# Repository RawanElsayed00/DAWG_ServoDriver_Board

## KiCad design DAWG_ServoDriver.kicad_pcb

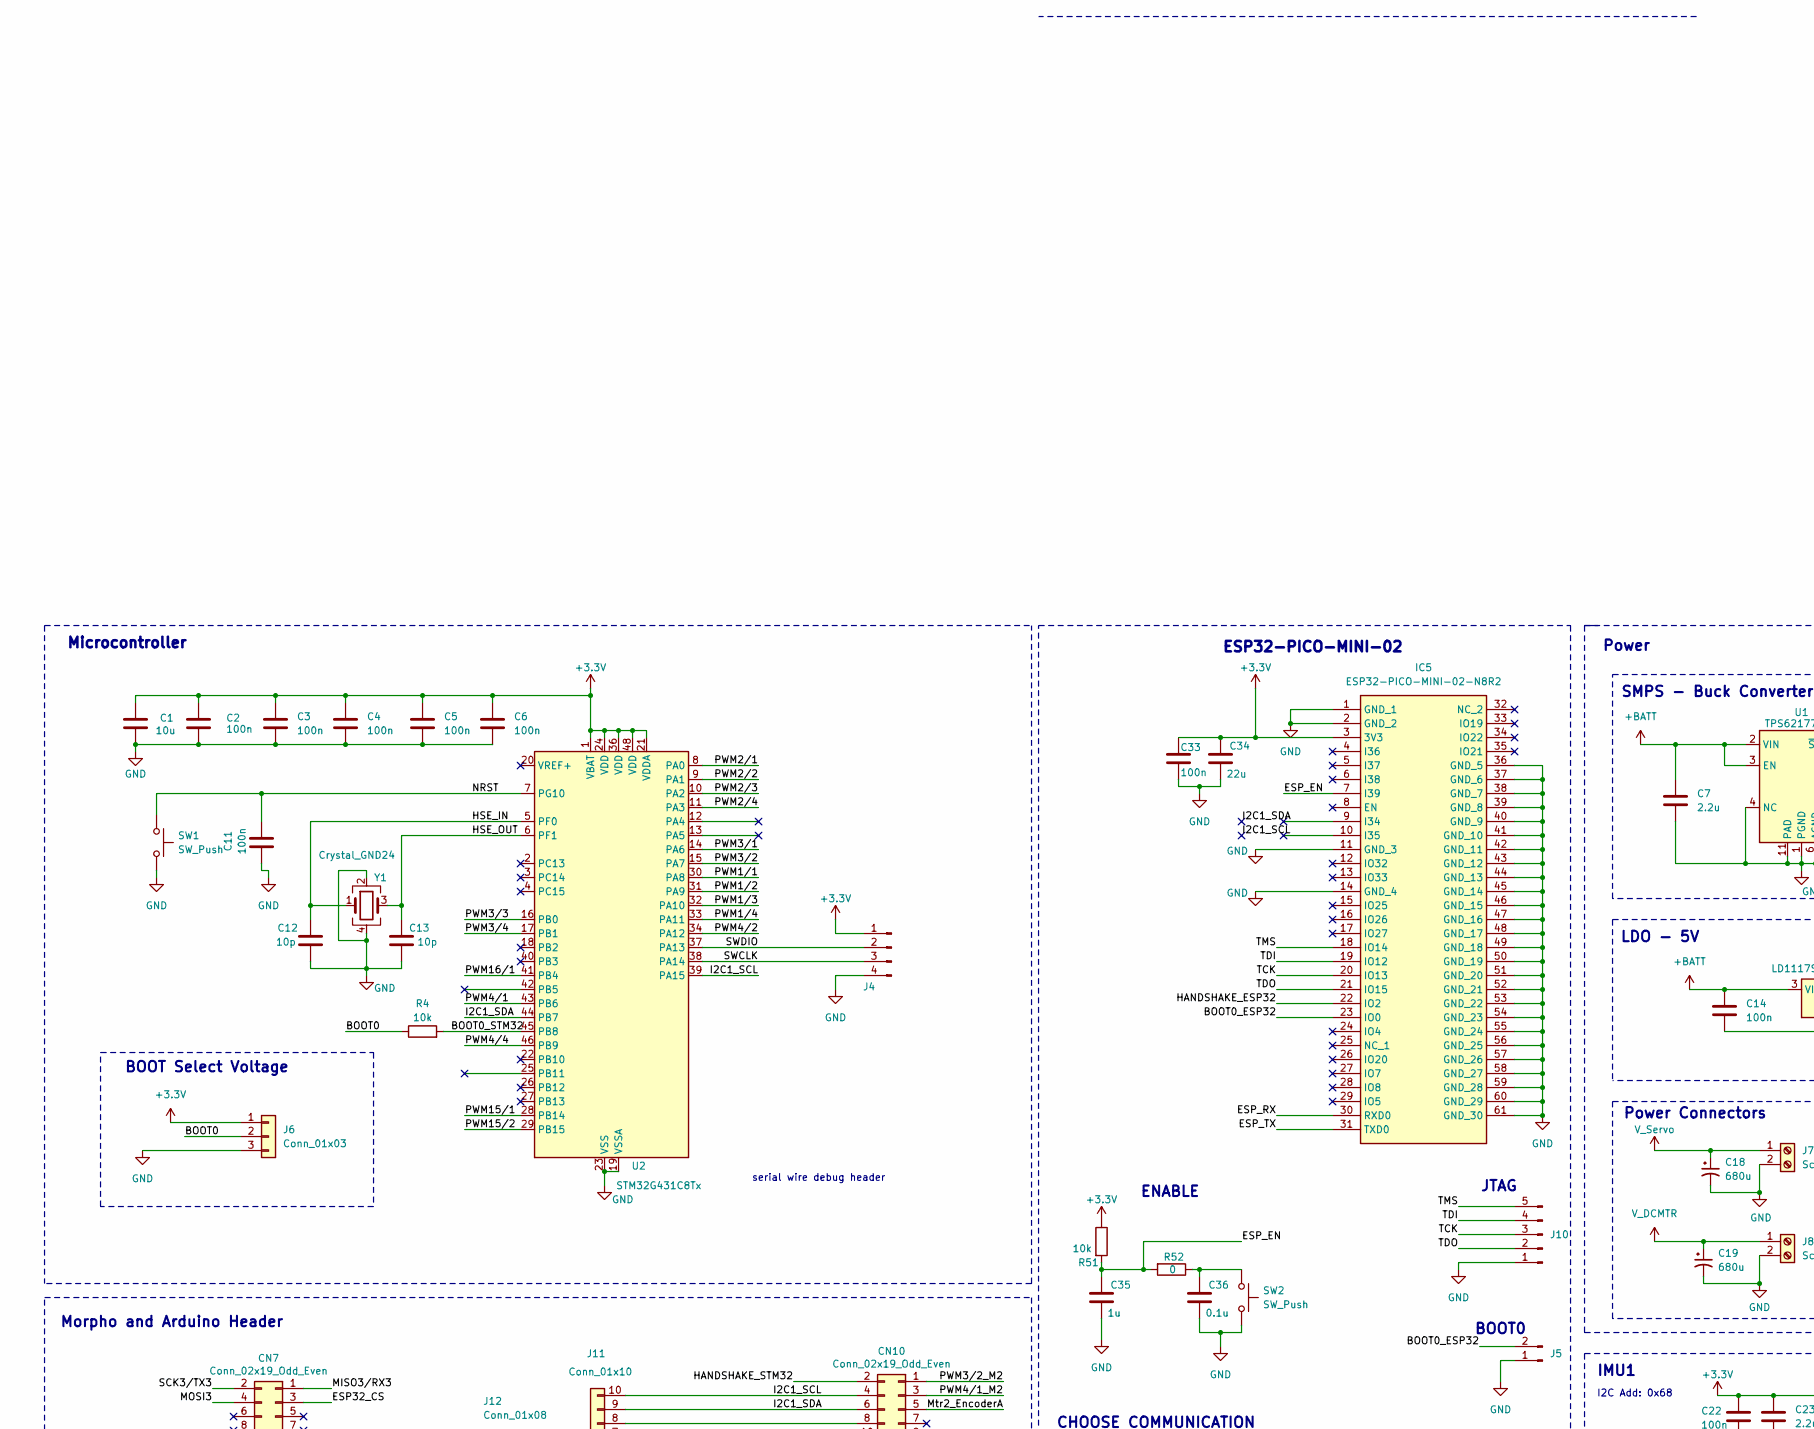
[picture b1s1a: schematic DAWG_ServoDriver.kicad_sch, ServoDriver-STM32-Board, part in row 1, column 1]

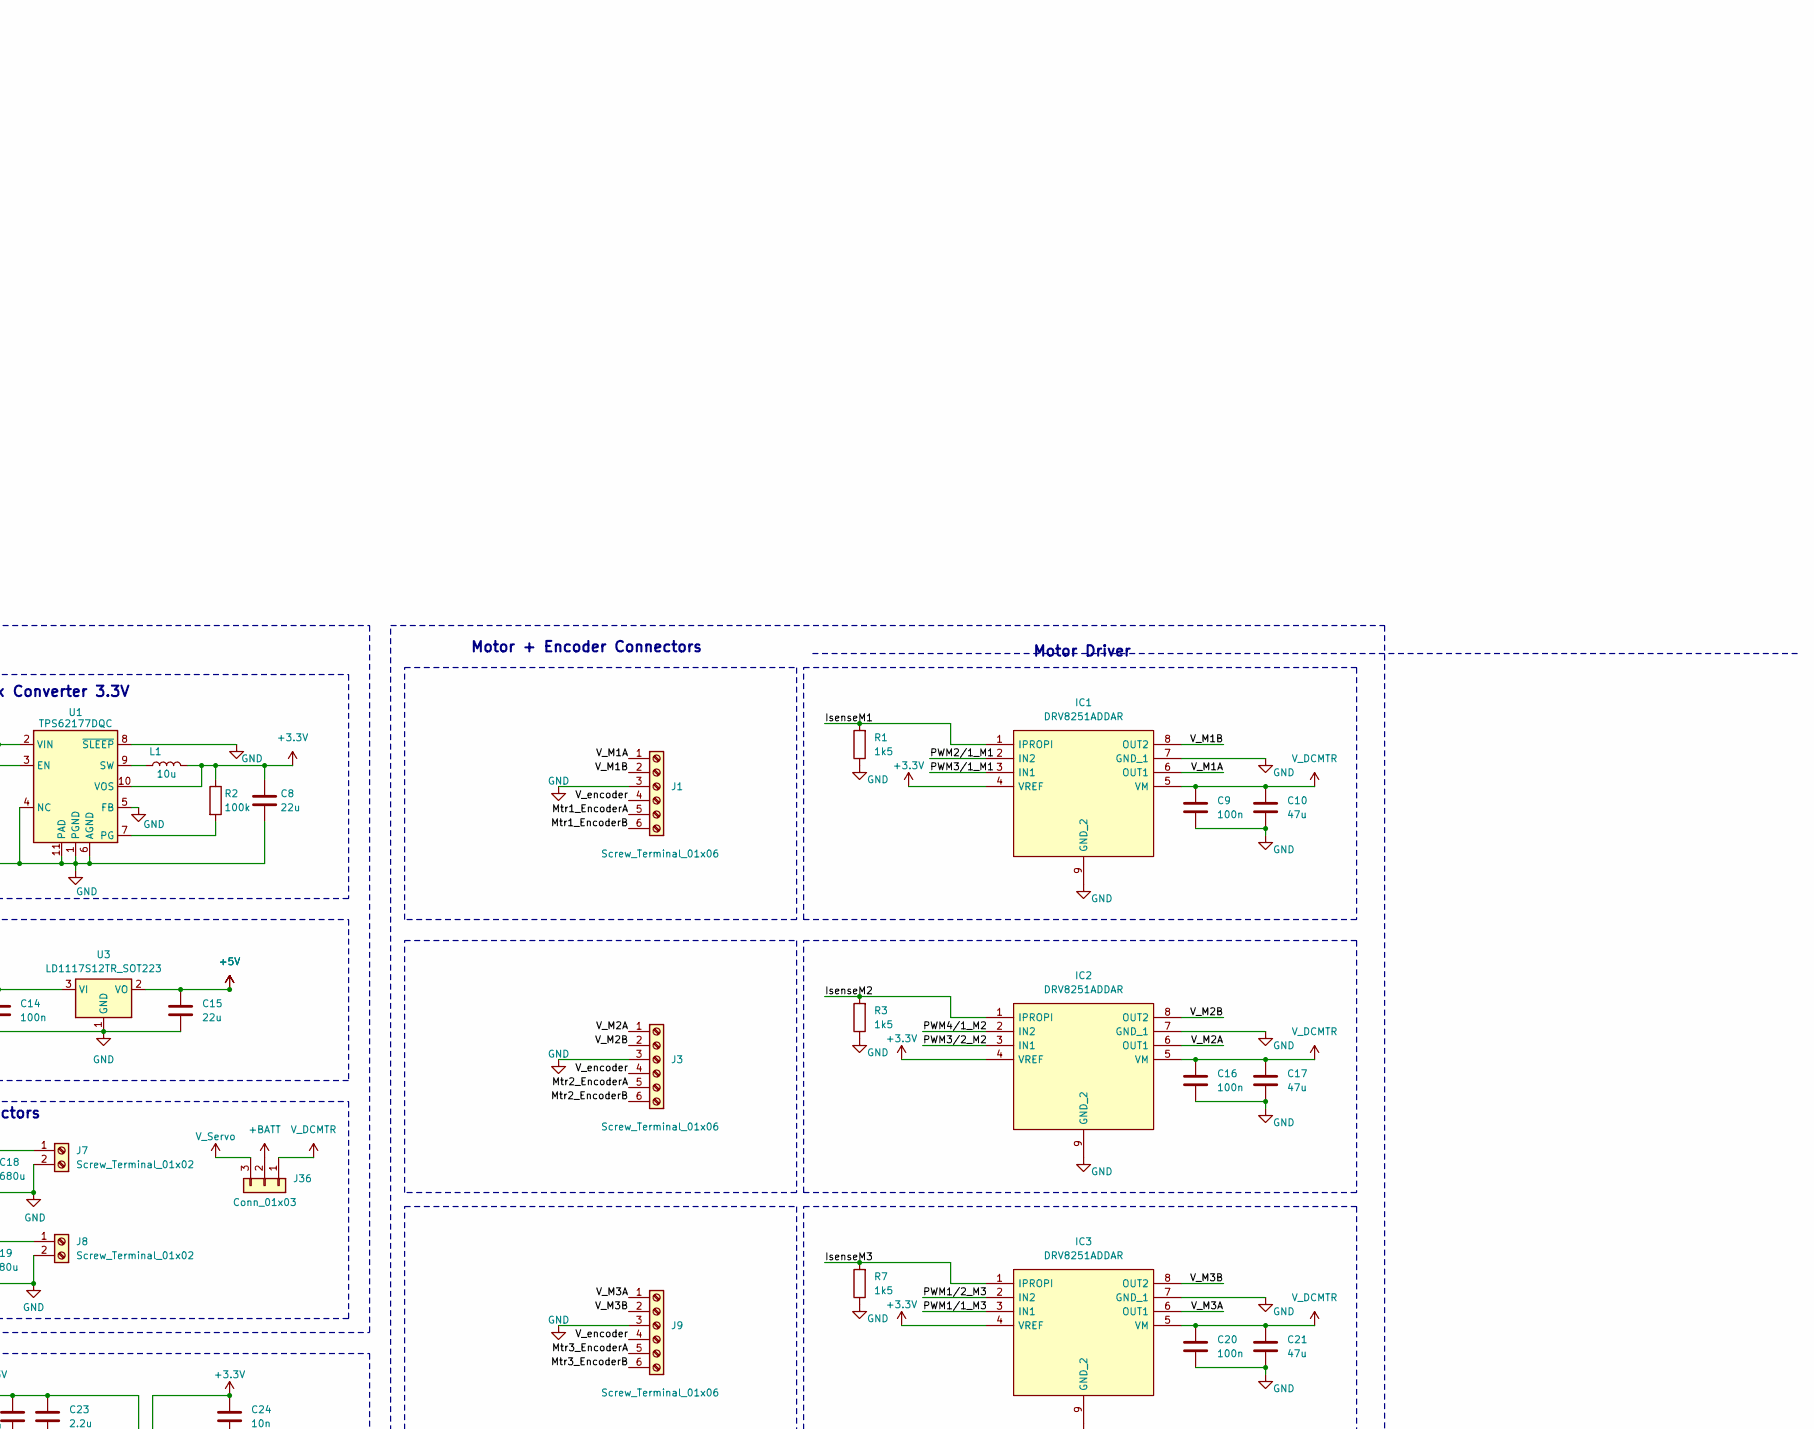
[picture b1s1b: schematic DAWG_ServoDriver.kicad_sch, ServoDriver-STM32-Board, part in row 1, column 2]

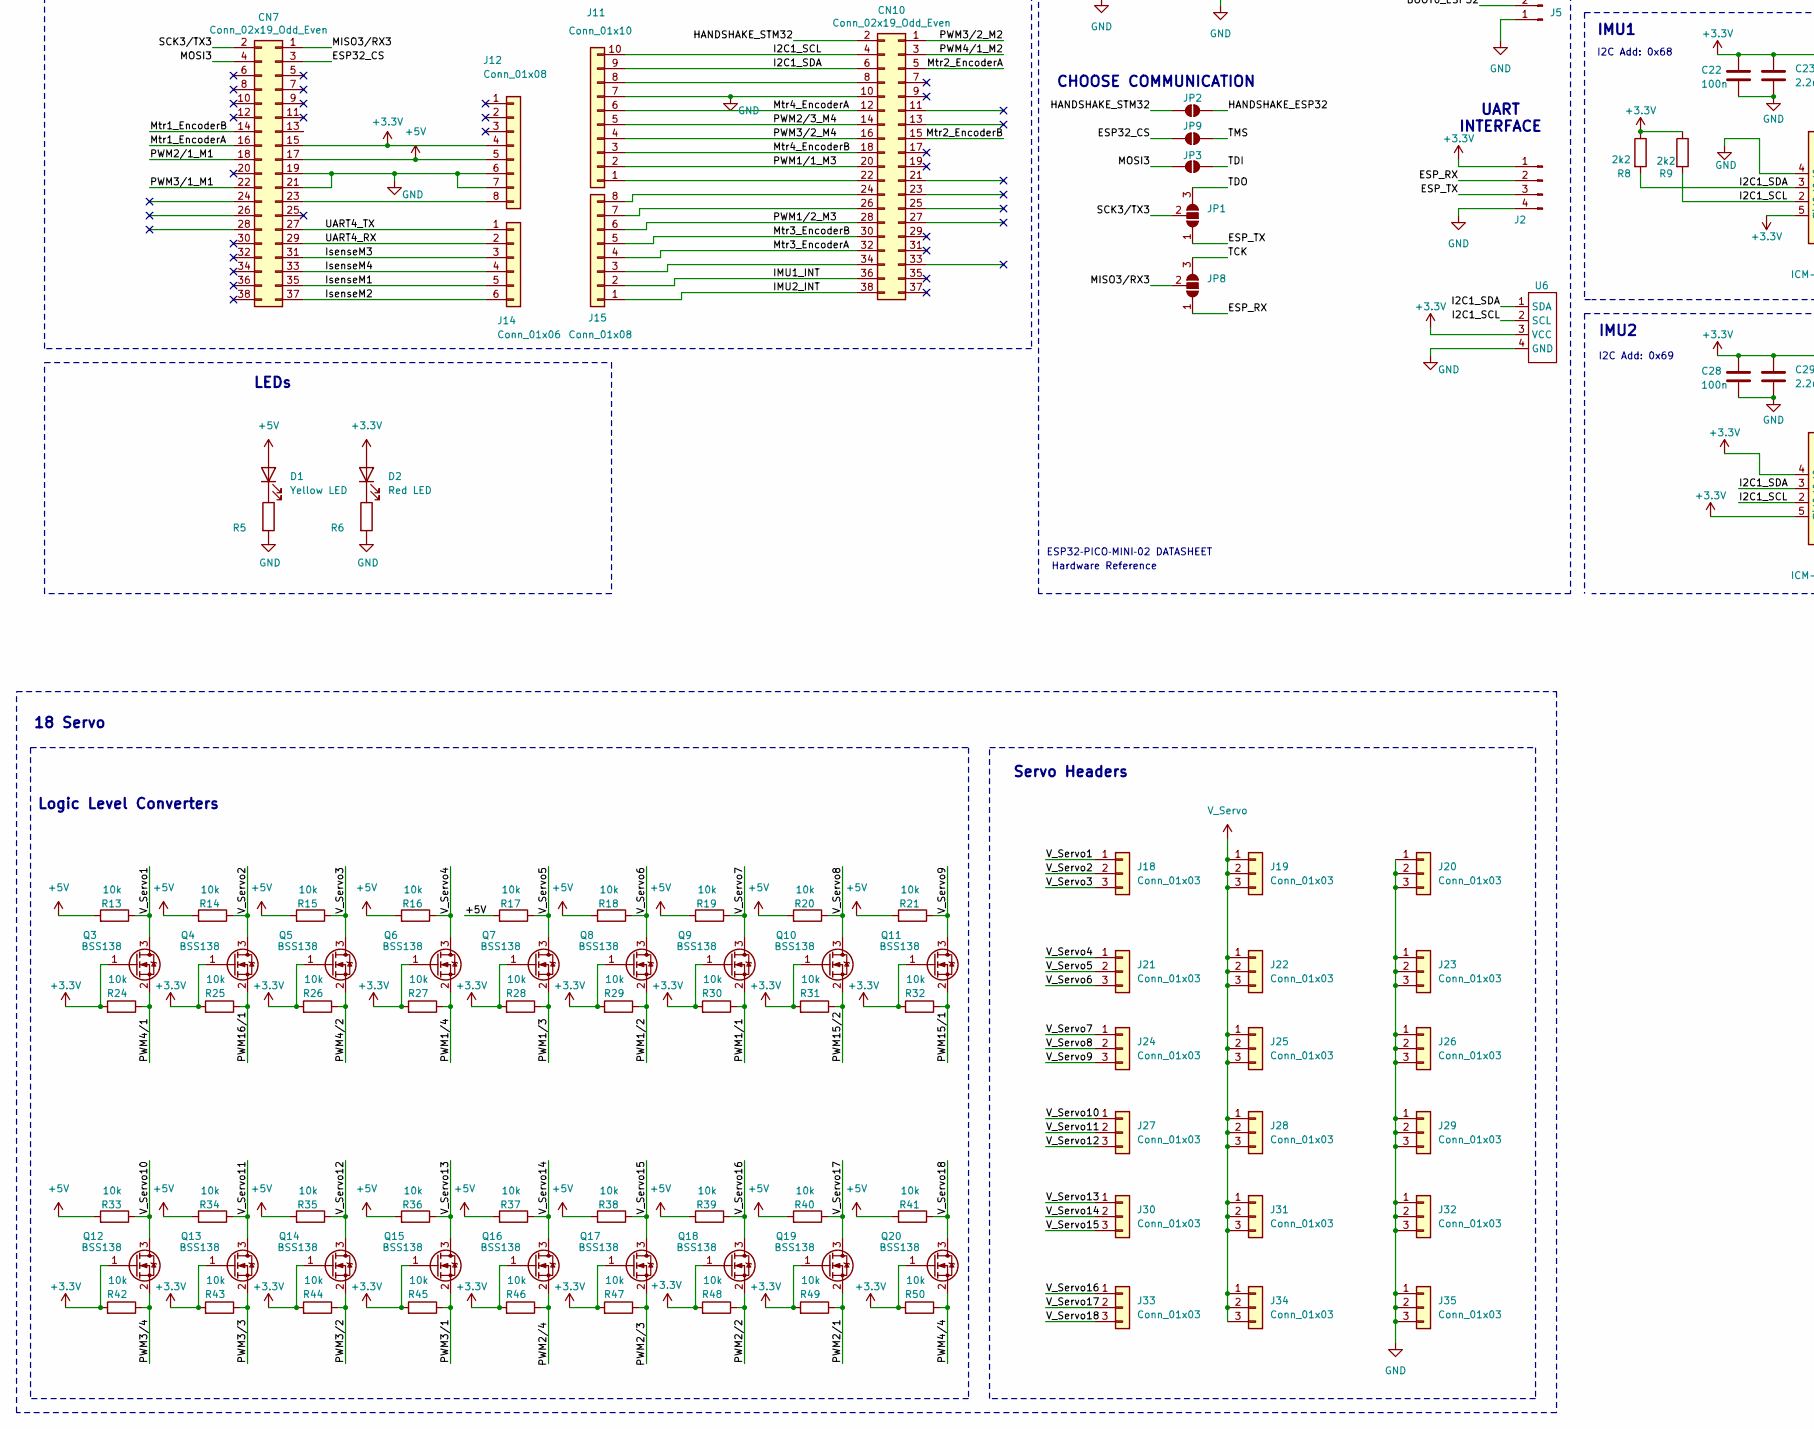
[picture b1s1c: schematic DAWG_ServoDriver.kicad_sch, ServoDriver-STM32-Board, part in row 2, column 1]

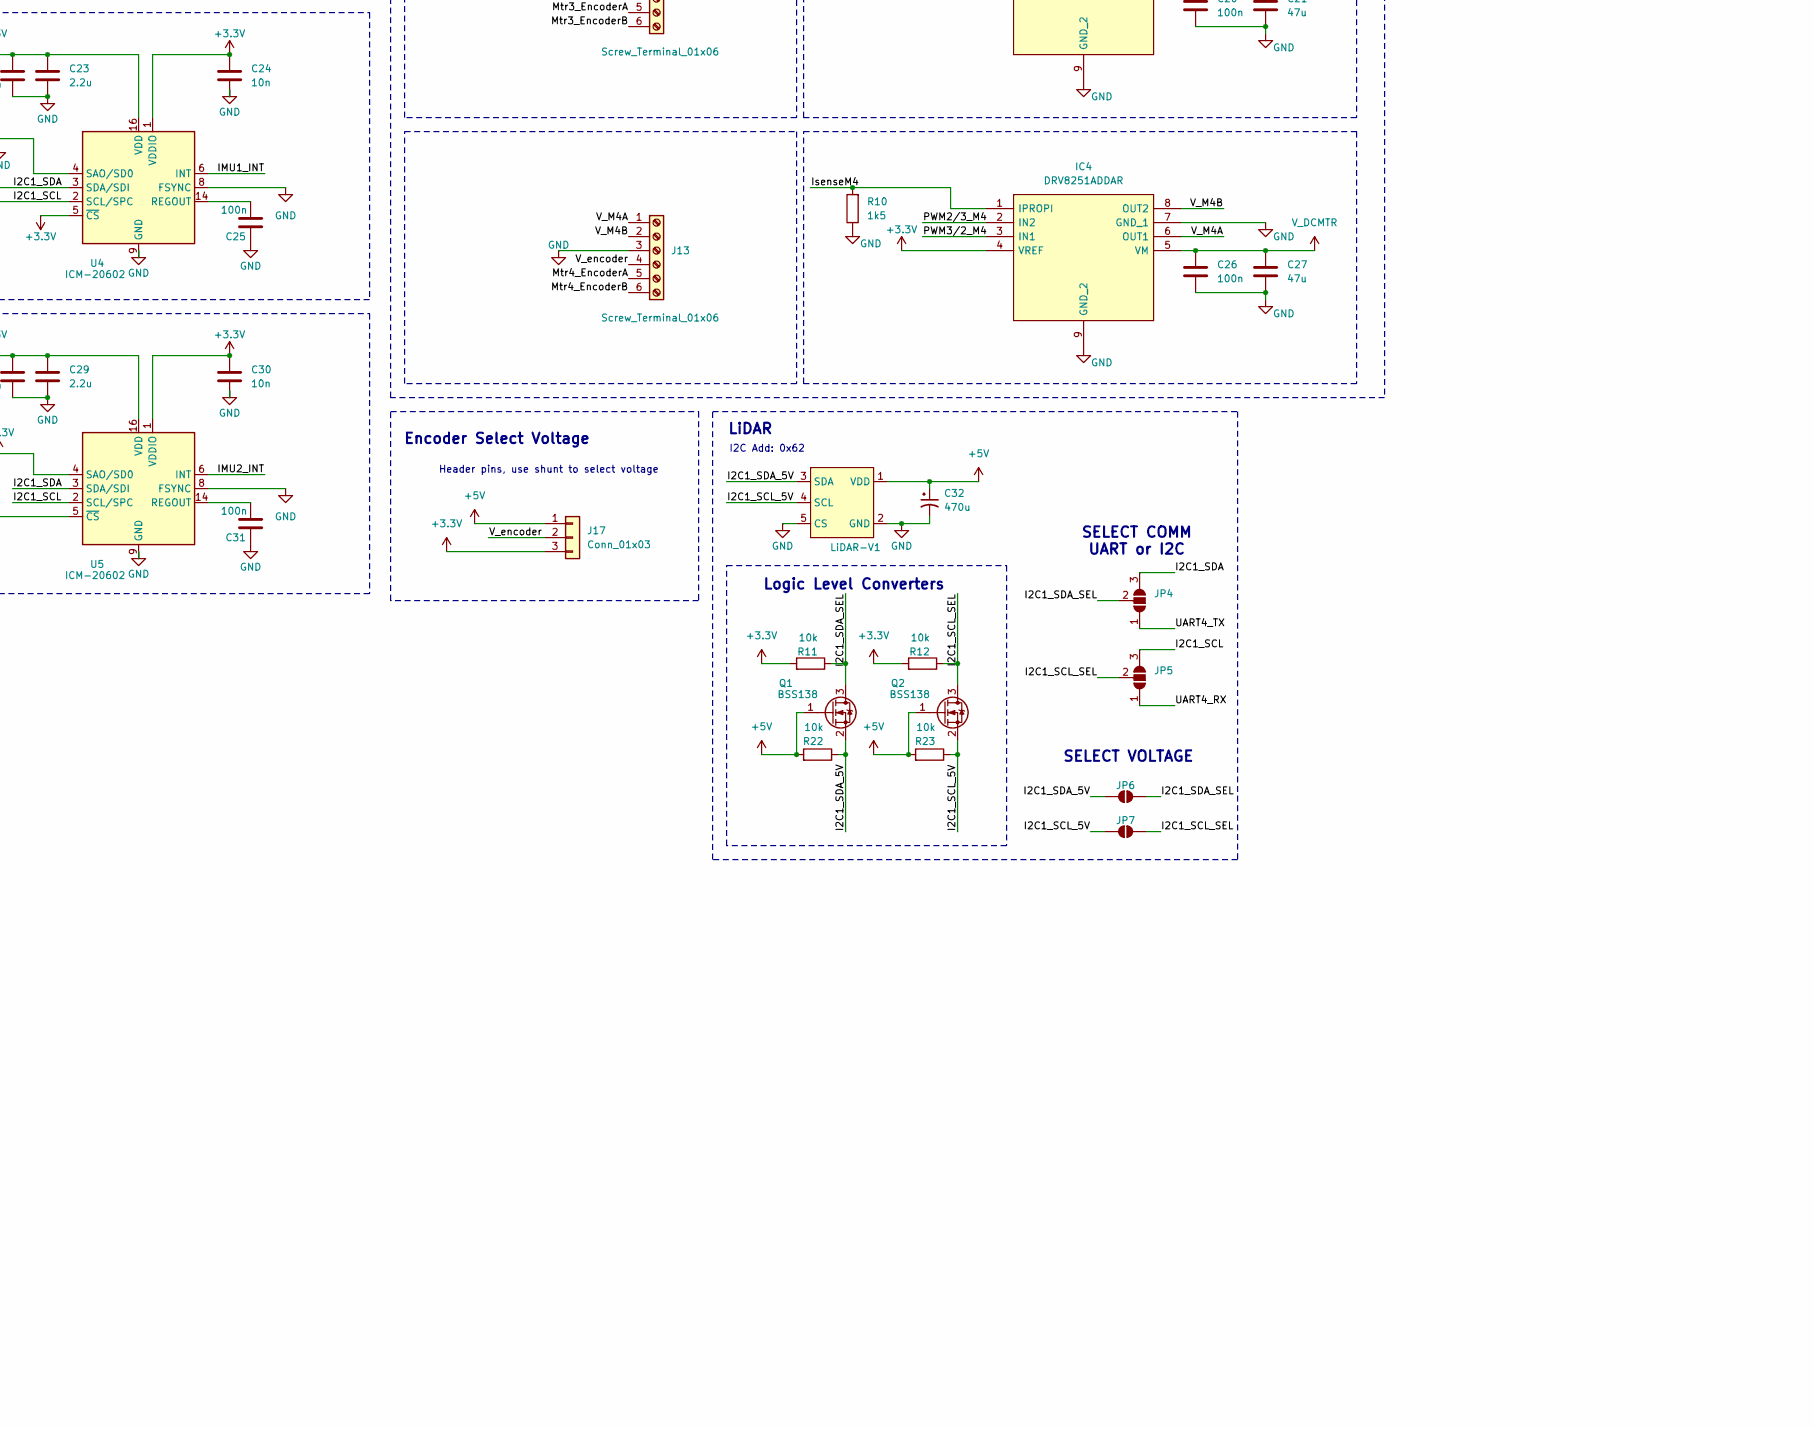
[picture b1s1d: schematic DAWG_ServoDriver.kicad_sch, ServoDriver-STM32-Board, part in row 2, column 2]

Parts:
C1: 10u; C_0402_1005Metric_Pad0.74x0.62mm_HandSolder
C2, C3, C4, C5, C6, C9, C11, C14, C16, C20, C22, C25, C26, C28, C31, C33: 100n; C_0402_1005Metric_Pad0.74x0.62mm_HandSolder
C7, C23, C29: 2.2u; C_0402_1005Metric_Pad0.74x0.62mm_HandSolder
C8, C15, C34: 22u; C_0402_1005Metric_Pad0.74x0.62mm_HandSolder
C10, C17, C21, C27: 47u; C_1206_3216Metric_Pad1.33x1.80mm_HandSolder
C12, C13: 10p; C_0402_1005Metric_Pad0.74x0.62mm_HandSolder
C18, C19: 680u; CP_Elec_10x10.5
C24, C30: 10n; C_0402_1005Metric_Pad0.74x0.62mm_HandSolder
C32: 470u; C_Radial_D6.3mm_H7.0mm_P2.50mm
C35: 1u; C_0402_1005Metric_Pad0.74x0.62mm_HandSolder
C36: 0.1u; C_0402_1005Metric_Pad0.74x0.62mm_HandSolder
CN7, CN10: Conn_02x19_Odd_Even; PinHeader_2x19_P2.54mm_Vertical
D1: Yellow LED; LED_0402_1005Metric_Pad0.77x0.64mm_HandSolder
D2: Red LED; LED_0402_1005Metric_Pad0.77x0.64mm_HandSolder
IC1, IC2, IC3, IC4: DRV8251ADDAR; SOIC127P600X170-9N; Mouser Part Number 595-DRV8251ADDAR
IC5: ESP32-PICO-MINI-02-N8R2; ESP32PICOMINI02N8R2; Mouser Part Number 356-ESP32PCOMN2PH3Q0
J1, J3, J9, J13: Screw_Terminal_01x06; TerminalBlock_TE_282834-6_1x06_P2.54mm_Horizontal
J2, J4: Conn_01x04_Pin; PinHeader_1x04_P2.54mm_Vertical
J5: Conn_01x02_Pin; PinHeader_1x02_P2.00mm_Vertical
J6, J17, J18, J19, J20, J21, J22, J23, J24, J25, J26, J27, J28, J29, J30, J31, J32, J33, J34, J35, J36: Conn_01x03; PinHeader_1x03_P2.54mm_Vertical
J7, J8: Screw_Terminal_01x02; TerminalBlock_MetzConnect_Type701_RT11L02HGLU_1x02_P6.35mm_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
J10: Conn_01x05_Pin; PinHeader_1x05_P2.54mm_Vertical
J11: Conn_01x10; PinHeader_1x10_P2.54mm_Vertical
J12, J15: Conn_01x08; PinHeader_1x08_P2.54mm_Vertical
J14: Conn_01x06; PinHeader_1x06_P2.54mm_Vertical
JP1, JP4, JP5, JP8: SolderJumper_3_Open; SolderJumper-3_P2.0mm_Open_TrianglePad1.0x1.5mm
JP2, JP3, JP6, JP7, JP9: SolderJumper_2_Open; SolderJumper-2_P1.3mm_Open_TrianglePad1.0x1.5mm
L1: 10u; L_0402_1005Metric_Pad0.77x0.64mm_HandSolder
LiDAR-V1: PinHeader_1x05_P2.54mm_Vertical
Q1, Q2, Q3, Q4, Q5, Q6, Q7, Q8, Q9, Q10, Q11, Q12, Q13, Q14, Q15, Q16, Q17, Q18, Q19, Q20: BSS138; SOT-23
R1, R3, R7, R10: 1k5; R_0402_1005Metric_Pad0.72x0.64mm_HandSolder
R2: 100k; R_0402_1005Metric_Pad0.72x0.64mm_HandSolder
R4, R11, R12, R13, R14, R15, R16, R17, R18, R19, R20, R21, R22, R23, R24, R25, R26, R27, R28, R29, R30, R31, R32, R33, R34, R35, R36, R37, R38, R39, R40, R41, R42, R43, R44, R45, R46, R47, R48, R49, R50, R51: 10k; R_0402_1005Metric_Pad0.72x0.64mm_HandSolder
R5, R6: 100; R_0402_1005Metric_Pad0.72x0.64mm_HandSolder
R8, R9: 2k2; R_0402_1005Metric_Pad0.72x0.64mm_HandSolder
R52: 0; R_0402_1005Metric_Pad0.72x0.64mm_HandSolder
SW1, SW2: SW_Push; SW_Push_1P1T-SH_NO_CK_KMR2xxG
U1: TPS62177DQC; WSON-10-1EP_2x3mm_P0.5mm_EP0.84x2.4mm_ThermalVias
U2: STM32G431C8Tx; LQFP-48_7x7mm_P0.5mm
U3: LD1117S12TR_SOT223; SOT-223-3_TabPin2
U4, U5: ICM-20602; LGA-16_3x3mm_P0.5mm_LayoutBorder3x5y
U6: LED_0.96inch
Y1: Crystal_GND24; Crystal_SMD_2016-4Pin_2.0x1.6mm

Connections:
+3.3V: C1.1, C2.1, C3.1, C4.1, C5.1, C6.1, C8.1, C22.1, C23.1, C24.1, C28.1, C29.1, C30.1, C33.2, C34.2, CN7.15, D2.2 (A), IC1.4 (VREF), IC2.4 (VREF), IC3.4 (VREF), IC4.4 (VREF), IC5.3 (3V3), J2.1, J4.1, J6.1, J12.4, J17.3, L1.2, Q3.1 (G), Q4.1 (G), Q5.1 (G), Q6.1 (G), Q7.1 (G), Q8.1 (G), Q9.1 (G), Q10.1 (G), Q11.1 (G), Q12.1 (G), Q13.1 (G), Q14.1 (G), Q15.1 (G), Q16.1 (G), Q17.1 (G), Q18.1 (G), Q19.1 (G), Q20.1 (G), R2.1, R8.1, R9.1, R11.2, R12.2, R24.2, R25.2, R26.2, R27.2, R28.2, R29.2, R30.2, R31.2, R32.2, R42.2, R43.2, R44.2, R45.2, R46.2, R47.2, R48.2, R49.2, R50.2, R51.1, U1.10 (VOS), U2.1 (VBAT), U2.21 (VDDA), U2.24 (VDD), U2.36 (VDD), U2.48 (VDD), U4.1 (VDDIO), U4.5 (~CS), U4.16 (VDD), U5.1 (VDDIO), U5.4 (SAO/SD0), U5.5 (~CS), U5.16 (VDD), U6.3 (VCC)
+5V: C15.2, C32.1, CN7.17, D1.2 (A), J12.5, J17.1, LiDAR-V1.1 (VDD), Q1.1 (G), Q2.1 (G), R13.2, R14.2, R15.2, R16.2, R17.2, R18.2, R19.2, R20.2, R21.2, R22.2, R23.2, R33.2, R34.2, R35.2, R36.2, R37.2, R38.2, R39.2, R40.2, R41.2, U3.2 (VO)
+BATT: C7.1, C14.2, J36.2, U1.2 (VIN), U1.3 (EN), U3.3 (VI)
/BOOT0: J6.2, R4.1
/BOOT0_ESP32: IC5.23 (IO0), J5.2; also elsewhere on the board
/BOOT0_STM32: R4.2, U2.45 (PB8)
/ESP32_CS: CN7.3, JP9.1 (A); also elsewhere on the board
/ESP_EN: C35.2, IC5.7 (I39), R51.2, R52.2
/ESP_RX: IC5.30 (RXD0), J2.2, JP8.1 (A); also elsewhere on the board
/ESP_TX: IC5.31 (TXD0), J2.3, JP1.1 (A); also elsewhere on the board
/HANDSHAKE_ESP32: IC5.22 (IO2), JP2.2 (B); also elsewhere on the board
/HANDSHAKE_STM32: CN10.2, JP2.1 (A); also elsewhere on the board
/HSE_IN: C12.1, U2.5 (PF0), Y1.1
/HSE_OUT: C13.1, U2.6 (PF1), Y1.3
/I2C1_SCL: CN10.4, J11.10, JP5.3 (B), R9.2, U2.39 (PA15), U4.2 (SCL/SPC), U5.2 (SCL/SPC), U6.2 (SCL); also elsewhere on the board
/I2C1_SCL_5V: JP7.1 (A), LiDAR-V1.4 (SCL), Q2.2 (S), R23.1; also elsewhere on the board
/I2C1_SCL_SEL: JP5.2 (C), JP7.2 (B), Q2.3 (D), R12.1; also elsewhere on the board
/I2C1_SDA: CN10.6, J11.9, JP4.3 (B), R8.2, U2.44 (PB7), U4.3 (SDA/SDI), U5.3 (SDA/SDI), U6.1 (SDA); also elsewhere on the board
/I2C1_SDA_5V: JP6.1 (A), LiDAR-V1.3 (SDA), Q1.2 (S), R22.1; also elsewhere on the board
/I2C1_SDA_SEL: JP4.2 (C), JP6.2 (B), Q1.3 (D), R11.1; also elsewhere on the board
/IMU1_INT: CN10.36, J15.2, U4.6 (INT)
/IMU2_INT: CN10.38, J15.1, U5.6 (INT)
/IsenseM1: CN7.35, IC1.1 (IPROPI), J14.5, R1.2
/IsenseM2: CN7.37, IC2.1 (IPROPI), J14.6, R3.2
/IsenseM3: CN7.31, IC3.1 (IPROPI), J14.3, R7.2
/IsenseM4: CN7.33, IC4.1 (IPROPI), J14.4, R10.2
/MISO3/RX3: CN7.1, JP8.2 (C); also elsewhere on the board
/MOSI3: CN7.4, JP3.1 (A); also elsewhere on the board
/Mtr1_EncoderA: CN7.16, J1.5
/Mtr1_EncoderB: CN7.14, J1.6
/Mtr2_EncoderA: CN10.5, J3.5
/Mtr2_EncoderB: CN10.15, J3.6
/Mtr3_EncoderA: CN10.32, J9.5, J15.4
/Mtr3_EncoderB: CN10.30, J9.6, J15.5
/Mtr4_EncoderA: CN10.12, J11.6, J13.5
/Mtr4_EncoderB: CN10.18, J11.3, J13.6
/NRST: C11.2, SW1.1, U2.7 (PG10)
/PWM1/1: Q9.2 (S), R30.1, U2.30 (PA8)
/PWM1/1_M3: CN10.20, IC3.3 (IN1), J11.2
/PWM1/2: Q8.2 (S), R29.1, U2.31 (PA9)
/PWM1/2_M3: CN10.28, IC3.2 (IN2), J15.6
/PWM1/3: Q7.2 (S), R28.1, U2.32 (PA10)
/PWM1/4: Q6.2 (S), R27.1, U2.33 (PA11)
/PWM2/1: Q19.2 (S), R49.1, U2.8 (PA0)
/PWM2/1_M1: CN7.18, IC1.2 (IN2)
/PWM2/2: Q18.2 (S), R48.1, U2.9 (PA1)
/PWM2/3: Q17.2 (S), R47.1, U2.10 (PA2)
/PWM2/3_M4: CN10.14, IC4.2 (IN2), J11.5
/PWM2/4: Q16.2 (S), R46.1, U2.11 (PA3)
/PWM3/1: Q15.2 (S), R45.1, U2.14 (PA6)
/PWM3/1_M1: CN7.22, IC1.3 (IN1)
/PWM3/2: Q14.2 (S), R44.1, U2.15 (PA7)
/PWM3/2_M2: CN10.1, IC2.3 (IN1)
/PWM3/2_M4: CN10.16, IC4.3 (IN1), J11.4
/PWM3/3: Q13.2 (S), R43.1, U2.16 (PB0)
/PWM3/4: Q12.2 (S), R42.1, U2.17 (PB1)
/PWM4/1: Q3.2 (S), R24.1, U2.43 (PB6)
/PWM4/1_M2: CN10.3, IC2.2 (IN2)
/PWM4/2: Q5.2 (S), R26.1, U2.34 (PA12)
/PWM4/4: Q20.2 (S), R50.1, U2.46 (PB9)
/PWM15/1: Q11.2 (S), R32.1, U2.28 (PB14)
/PWM15/2: Q10.2 (S), R31.1, U2.29 (PB15)
/PWM16/1: Q4.2 (S), R25.1, U2.41 (PB4)
/SCK3/TX3: CN7.2, JP1.2 (C); also elsewhere on the board
/SWCLK: J4.3, U2.38 (PA14)
/SWDIO: J4.2, U2.37 (PA13)
/TCK: IC5.20 (IO13), J10.3, JP8.3 (B); also elsewhere on the board
/TDI: IC5.19 (IO12), J10.4, JP3.2 (B); also elsewhere on the board
/TDO: IC5.21 (IO15), J10.2, JP1.3 (B); also elsewhere on the board
/TMS: IC5.18 (IO14), J10.5, JP9.2 (B); also elsewhere on the board
/UART4_RX: CN7.29, J14.2, JP5.1 (A); also elsewhere on the board
/UART4_TX: CN7.27, J14.1, JP4.1 (A); also elsewhere on the board
/V_M1A: IC1.6 (OUT1), J1.1
/V_M1B: IC1.8 (OUT2), J1.2
/V_M2A: IC2.6 (OUT1), J3.1
/V_M2B: IC2.8 (OUT2), J3.2
/V_M3A: IC3.6 (OUT1), J9.1
/V_M3B: IC3.8 (OUT2), J9.2
/V_M4A: IC4.6 (OUT1), J13.1
/V_M4B: IC4.8 (OUT2), J13.2
/V_Servo1: J18.1, Q3.3 (D), R13.1
/V_Servo2: J18.2, Q4.3 (D), R14.1
/V_Servo3: J18.3, Q5.3 (D), R15.1
/V_Servo4: J21.1, Q6.3 (D), R16.1
/V_Servo5: J21.2, Q7.3 (D), R17.1
/V_Servo6: J21.3, Q8.3 (D), R18.1
/V_Servo7: J24.1, Q9.3 (D), R19.1
/V_Servo8: J24.2, Q10.3 (D), R20.1
/V_Servo9: J24.3, Q11.3 (D), R21.1
/V_Servo10: J27.1, Q12.3 (D), R33.1
/V_Servo11: J27.2, Q13.3 (D), R34.1
/V_Servo12: J27.3, Q14.3 (D), R35.1
/V_Servo13: J30.1, Q15.3 (D), R36.1
/V_Servo14: J30.2, Q16.3 (D), R37.1
/V_Servo15: J30.3, Q17.3 (D), R38.1
/V_Servo16: J33.1, Q18.3 (D), R39.1
/V_Servo17: J33.2, Q19.3 (D), R40.1
/V_Servo18: J33.3, Q20.3 (D), R41.1
/V_encoder: J1.4, J3.4, J9.4, J13.4, J17.2
GND: C1.2, C2.2, C3.2, C4.2, C5.2, C6.2, C7.2, C8.2, C9.1, C10.1, C11.1, C12.2, C13.2, C14.1, C15.1, C16.1, C17.1, C18.2, C19.2, C20.1, C21.1, C22.2, C23.2, C24.2, C25.1, C26.1, C27.1, C28.2, C29.2, C30.2, C31.1, C32.2, C33.1, C34.1, C35.1, C36.1, CN7.19, CN7.21, CN10.10, IC1.7 (GND_1), IC1.9 (GND_2), IC2.7 (GND_1), IC2.9 (GND_2), IC3.7 (GND_1), IC3.9 (GND_2), IC4.7 (GND_1), IC4.9 (GND_2), IC5.1 (GND_1), IC5.2 (GND_2), IC5.11 (GND_3), IC5.14 (GND_4), IC5.36 (GND_5), IC5.37 (GND_6), IC5.38 (GND_7), IC5.39 (GND_8), IC5.40 (GND_9), IC5.41 (GND_10), IC5.42 (GND_11), IC5.43 (GND_12), IC5.44 (GND_13), IC5.45 (GND_14), IC5.46 (GND_15), IC5.47 (GND_16), IC5.48 (GND_17), IC5.49 (GND_18), IC5.50 (GND_19), IC5.51 (GND_20), IC5.52 (GND_21), IC5.53 (GND_22), IC5.54 (GND_23), IC5.55 (GND_24), IC5.56 (GND_25), IC5.57 (GND_26), IC5.58 (GND_27), IC5.59 (GND_28), IC5.60 (GND_29), IC5.61 (GND_30), J1.3, J2.4, J3.3, J4.4, J5.1, J6.3, J7.2, J8.2, J9.3, J10.1, J11.7, J12.6, J12.7, J13.3, J20.1, J20.2, J20.3, J23.1, J23.2, J23.3, J26.1, J26.2, J26.3, J29.1, J29.2, J29.3, J32.1, J32.2, J32.3, J35.1, J35.2, J35.3, LiDAR-V1.2 (GND), LiDAR-V1.5 (CS), R1.1, R3.1, R5.2, R6.2, R7.1, R10.1, SW1.2, SW2.2, U1.1 (PGND), U1.4 (NC), U1.5 (FB), U1.6 (AGND), U1.8 (~SLEEP), U1.11 (PAD), U2.19 (VSSA), U2.23 (VSS), U2.35 (VSS), U2.47 (VSS), U3.1 (GND), U4.4 (SAO/SD0), U4.8 (FSYNC), U4.9 (GND), U4.10 (GND), U4.11 (GND), U4.12 (GND), U4.13 (GND), U4.15 (GND), U5.8 (FSYNC), U5.9 (GND), U5.10 (GND), U5.11 (GND), U5.12 (GND), U5.13 (GND), U5.15 (GND), U6.4 (GND), Y1.2, Y1.4; also elsewhere on the board
unnamed 100: C36.2, R52.1, SW2.1; also elsewhere on the board
unnamed: CN7.23, J12.8
unnamed: CN10.8, J11.8
unnamed: CN10.22, J11.1
unnamed: CN10.24, J15.8
unnamed: CN10.26, J15.7
unnamed: CN10.34, J15.3
unnamed: D1.1 (K), R5.1
unnamed: D2.1 (K), R6.1
unnamed: R2.2, U1.7 (PG)
unnamed: L1.1, U1.9 (SW)
unnamed: C25.2, U4.14 (REGOUT)
unnamed: C31.2, U5.14 (REGOUT)
V_DCMTR: C9.2, C10.2, C16.2, C17.2, C19.1, C20.2, C21.2, C26.2, C27.2, IC1.5 (VM), IC2.5 (VM), IC3.5 (VM), IC4.5 (VM), J8.1, J36.1
V_Servo: C18.1, J7.1, J19.1, J19.2, J19.3, J22.1, J22.2, J22.3, J25.1, J25.2, J25.3, J28.1, J28.2, J28.3, J31.1, J31.2, J31.3, J34.1, J34.2, J34.3, J36.3

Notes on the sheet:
Motor + Encoder Connectors
Servo Headers
Logic Level Converters
Power Connectors
ESP32-PICO-MINI-02
Encoder Select Voltage
SELECT VOLTAGE
UART INTERFACE
I2C Add: 0x69
LiDAR
SELECT COMM UART or I2C
LDO - 5V
ESP32­PICO­MINI­02 DATASHEET
BOOT Select Voltage
IMU2
LEDs
Hardware Reference
Logic Level Converters
JTAG
serial wire debug header
I2C Add: 0x62
Power
SMPS - Buck Converter 3.3V
ENABLE
I2C Add: 0x68
Header pins, use shunt to select voltage
Motor Driver
BOOT0
CHOOSE COMMUNICATION
Microcontroller
IMU1
18 Servo
Morpho and Arduino Header

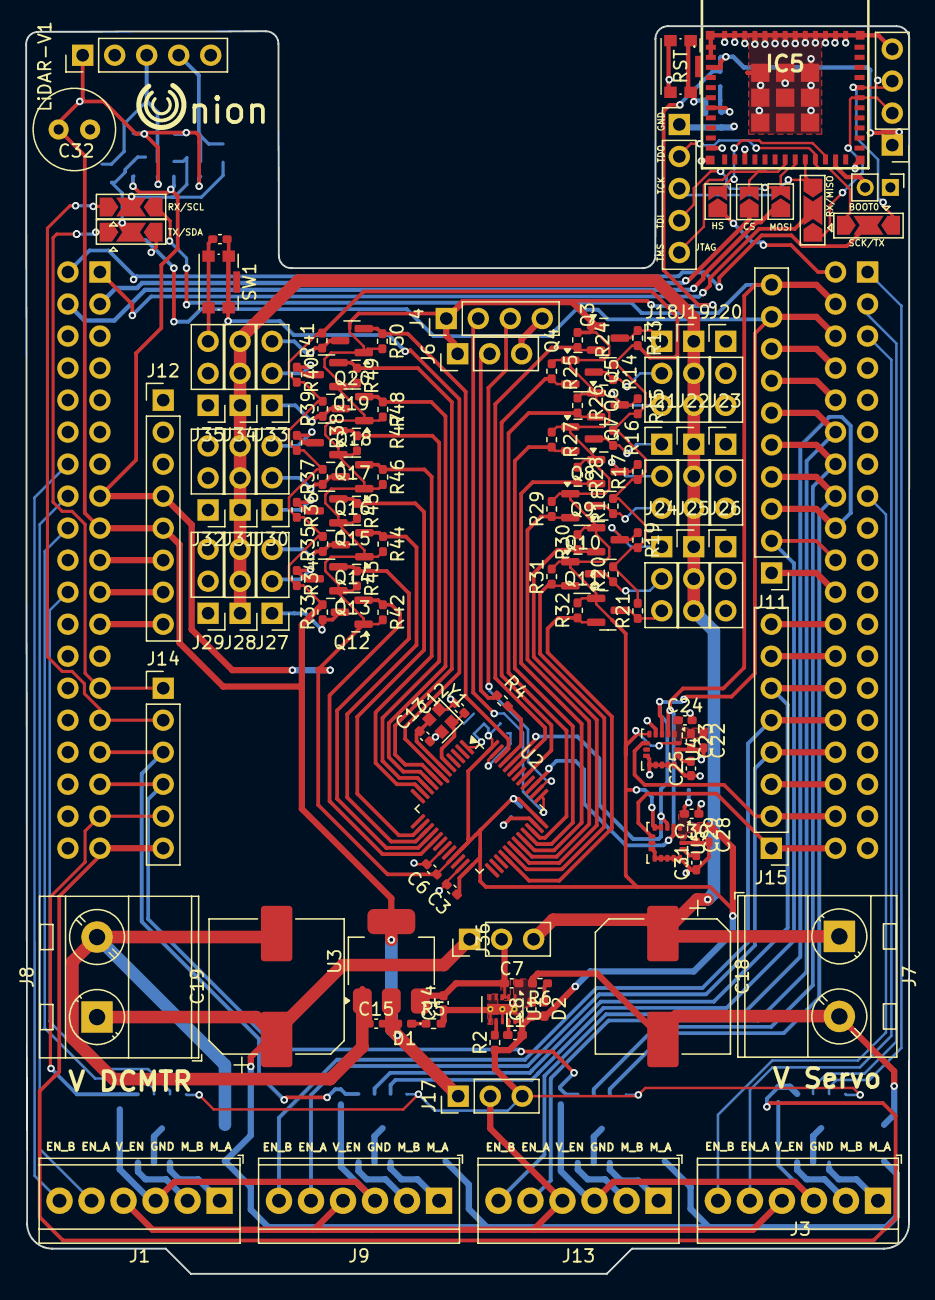
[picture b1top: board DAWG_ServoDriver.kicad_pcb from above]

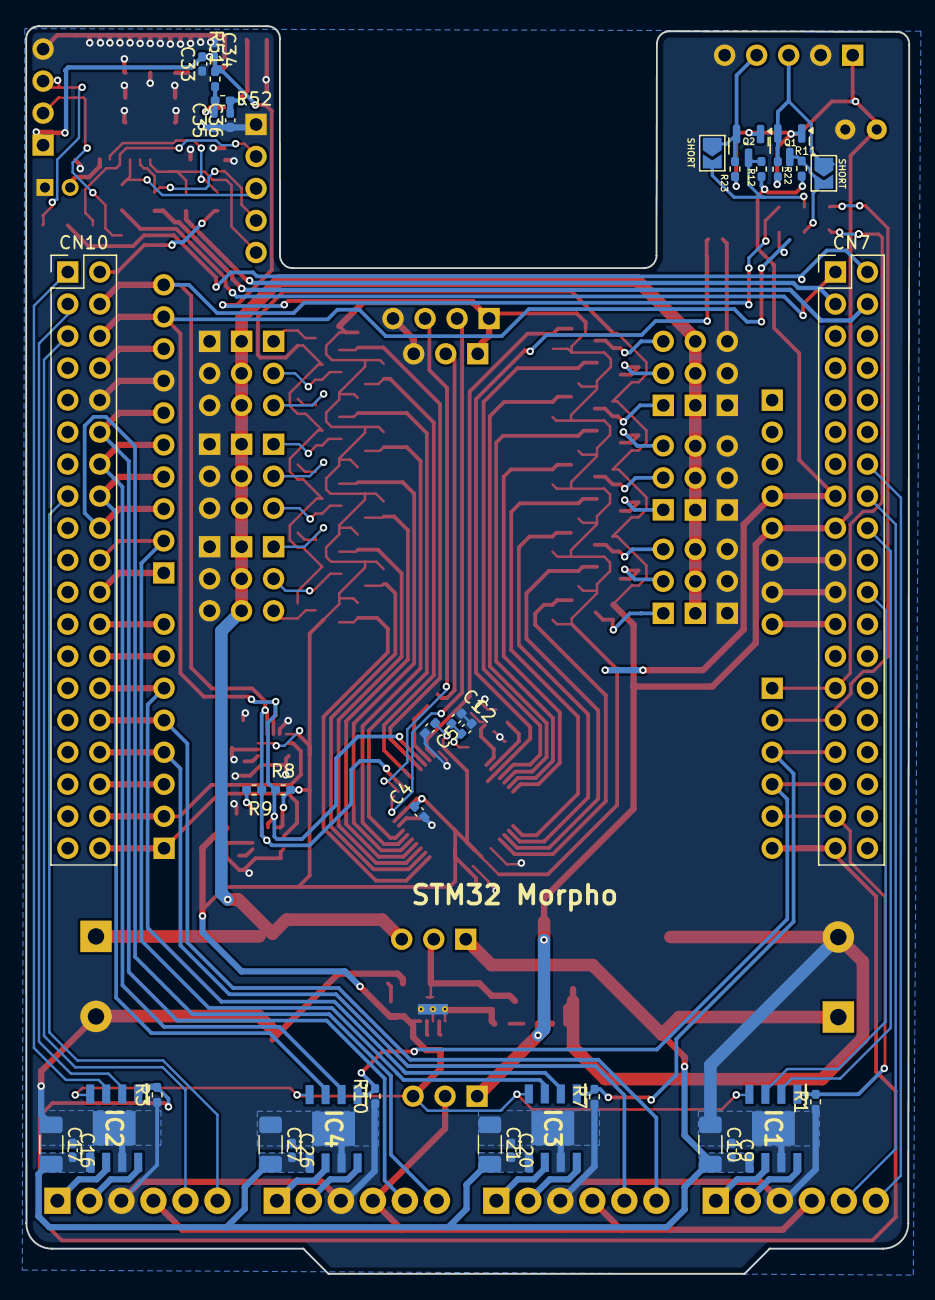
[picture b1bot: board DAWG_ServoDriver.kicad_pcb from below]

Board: 2 copper layers, 70.1 x 99.0 mm, 171 parts (38 on the bottom side), 115 nets.

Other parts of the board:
BOOT0: Conn_01x02_Pin; PinHeader_1x02_P2.00mm_Vertical
CS: SolderJumper_2_Open; SolderJumper-2_P1.3mm_Open_TrianglePad1.0x1.5mm
HS: SolderJumper_2_Open; SolderJumper-2_P1.3mm_Open_TrianglePad1.0x1.5mm
JTAG: Conn_01x05_Pin; PinHeader_1x05_P2.54mm_Vertical
MOSI: SolderJumper_2_Open; SolderJumper-2_P1.3mm_Open_TrianglePad1.0x1.5mm
RST: SW_Push; SW_Push_1P1T-SH_NO_CK_KMR2xxG
RX/MISO: SolderJumper_3_Open; SolderJumper-3_P2.0mm_Open_TrianglePad1.0x1.5mm
RX/SCL: SolderJumper_3_Open; SolderJumper-3_P2.0mm_Open_TrianglePad1.0x1.5mm
SCK/TX: SolderJumper_3_Open; SolderJumper-3_P2.0mm_Open_TrianglePad1.0x1.5mm
SHORT: SolderJumper_2_Open; SolderJumper-2_P1.3mm_Open_TrianglePad1.0x1.5mm
SHORT#2: SolderJumper_2_Open; SolderJumper-2_P1.3mm_Open_TrianglePad1.0x1.5mm
TX/SDA: SolderJumper_3_Open; SolderJumper-3_P2.0mm_Open_TrianglePad1.0x1.5mm

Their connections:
/BOOT0_ESP32: BOOT0.2; also elsewhere on the board
/ESP32_CS: CS.1 (A); also elsewhere on the board
/ESP_RX: RX/MISO.1 (A); also elsewhere on the board
/ESP_TX: SCK/TX.1 (A); also elsewhere on the board
/HANDSHAKE_ESP32: HS.2 (B); also elsewhere on the board
/HANDSHAKE_STM32: HS.1 (A); also elsewhere on the board
/I2C1_SCL: RX/SCL.3 (B); also elsewhere on the board
/I2C1_SCL_5V: SHORT#2.1 (A); also elsewhere on the board
/I2C1_SCL_SEL: RX/SCL.2 (C), SHORT#2.2 (B); also elsewhere on the board
/I2C1_SDA: TX/SDA.3 (B); also elsewhere on the board
/I2C1_SDA_5V: SHORT.1 (A); also elsewhere on the board
/I2C1_SDA_SEL: SHORT.2 (B), TX/SDA.2 (C); also elsewhere on the board
/MISO3/RX3: RX/MISO.2 (C); also elsewhere on the board
/MOSI3: MOSI.1 (A); also elsewhere on the board
/SCK3/TX3: SCK/TX.2 (C); also elsewhere on the board
/TCK: JTAG.3, RX/MISO.3 (B); also elsewhere on the board
/TDI: JTAG.4, MOSI.2 (B); also elsewhere on the board
/TDO: JTAG.2, SCK/TX.3 (B); also elsewhere on the board
/TMS: CS.2 (B), JTAG.5; also elsewhere on the board
/UART4_RX: RX/SCL.1 (A); also elsewhere on the board
/UART4_TX: TX/SDA.1 (A); also elsewhere on the board
GND: BOOT0.1, JTAG.1, RST.2; also elsewhere on the board
unnamed 100: RST.1; also elsewhere on the board

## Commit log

2024-04-06 Initial Commit Schematic Draft
2024-04-06 feedback
2024-04-07 Your commit message
2024-04-07 Updated IMU, Added Motor Drivers and screw terminal, Added the morpho header
2024-04-07 Added motor driver resistor values and arranged components
2024-04-08 Added footprints for all except SW1, SW2, ServoHeader, crystal
2024-04-08 Added Arduino connectors and LEDs. Changed servo footprint and power in labels.
2024-04-08 Started PCB, alligned and placed microcontroller components
2024-04-09 Placed mos most components, routed servo.
2024-04-11 Finished Routing all except IMU2_INT and GNDs
2024-04-18 Key components placed, Onion board begins.
2024-04-27 Cosmetic changes
2024-05-08 Merges pull request
2024-05-09 added esp32 & lidar, finished routing unrouted stuff
2024-05-09 added selectable I2C/UART for peripheral (LIDAR), added some annotation for soldermaks
2024-05-09 cleaned onion
2024-05-09 onion merge
2024-05-09 DS store
2024-05-09 ignore DS_Store
